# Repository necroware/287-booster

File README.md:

# 287 Booster

This is an interposer which adds a jumper which can be used to select the clock
divider on a 287 floating point unit. It was designed and open sourced in
cooperation with the user i440bx from the German dosreloaded.de community.

## Background

Intel 287 co-processors have configuration pin 39 for the clock mode signal
(CKM) setup. When this pin is pulled up the chip will use the clock directly. If
it is pulled to ground the chip will use a clock divider. The pin has internal
pull-down resistor, so it can be left unconnected, which will default the
setting to divided clock. Which divider will be used depends on the chip:

- Intel D80287, M80287 run at 1/3 of the clock
- Intel i287XL runs at 1/2 of the clock
- AMD D80C287 runs at 1/3 of the clock

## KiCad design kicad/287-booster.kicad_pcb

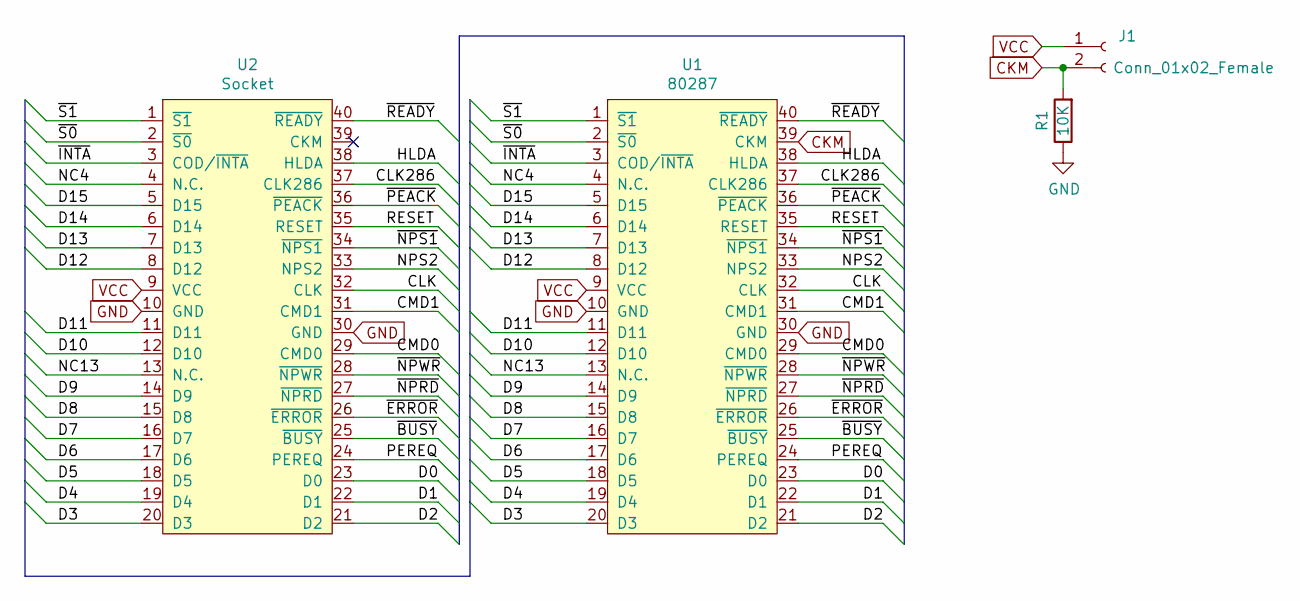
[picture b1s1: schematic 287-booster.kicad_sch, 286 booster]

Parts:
J1: Conn_01x02_Female; PinHeader_1x02_P2.54mm_Vertical
R1: 10K; R_Axial_DIN0207_L6.3mm_D2.5mm_P7.62mm_Horizontal
U1: 80287; DIP-40_W15.24mm_Socket
U2: Socket; DIP-40_W15.24mm

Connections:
/CLK: U1.32 (CLK), U2.32 (CLK)
/CLK286: U1.37 (CLK286), U2.37 (CLK286)
/CMD0: U1.29 (CMD0), U2.29 (CMD0)
/CMD1: U1.31 (CMD1), U2.31 (CMD1)
/D0: U1.23 (D0), U2.23 (D0)
/D1: U1.22 (D1), U2.22 (D1)
/D2: U1.21 (D2), U2.21 (D2)
/D3: U1.20 (D3), U2.20 (D3)
/D4: U1.19 (D4), U2.19 (D4)
/D5: U1.18 (D5), U2.18 (D5)
/D6: U1.17 (D6), U2.17 (D6)
/D7: U1.16 (D7), U2.16 (D7)
/D8: U1.15 (D8), U2.15 (D8)
/D9: U1.14 (D9), U2.14 (D9)
/D10: U1.12 (D10), U2.12 (D10)
/D11: U1.11 (D11), U2.11 (D11)
/D12: U1.8 (D12), U2.8 (D12)
/D13: U1.7 (D13), U2.7 (D13)
/D14: U1.6 (D14), U2.6 (D14)
/D15: U1.5 (D15), U2.5 (D15)
/HLDA: U1.38 (HLDA), U2.38 (HLDA)
/NC4: U1.4 (N.C.), U2.4 (N.C.)
/NC13: U1.13 (N.C.), U2.13 (N.C.)
/NPS2: U1.33 (NPS2), U2.33 (NPS2)
/PEREQ: U1.24 (PEREQ), U2.24 (PEREQ)
/RESET: U1.35 (RESET), U2.35 (RESET)
/~BUSY: U1.25 (~BUSY), U2.25 (~BUSY)
/~ERROR: U1.26 (~ERROR), U2.26 (~ERROR)
/~INTA: U1.3 (COD/~INTA), U2.3 (COD/~INTA)
/~NPRD: U1.27 (~NPRD), U2.27 (~NPRD)
/~NPS1: U1.34 (~NPS1), U2.34 (~NPS1)
/~NPWR: U1.28 (~NPWR), U2.28 (~NPWR)
/~PEACK: U1.36 (~PEACK), U2.36 (~PEACK)
/~READY: U1.40 (~READY), U2.40 (~READY)
/~S0: U1.2 (~S0), U2.2 (~S0)
/~S1: U1.1 (~S1), U2.1 (~S1)
CKM: J1.2, R1.2, U1.39 (CKM)
GND: R1.1, U1.10 (GND), U1.30 (GND), U2.10 (GND), U2.30 (GND)
VCC: J1.1, U1.9 (VCC), U2.9 (VCC)

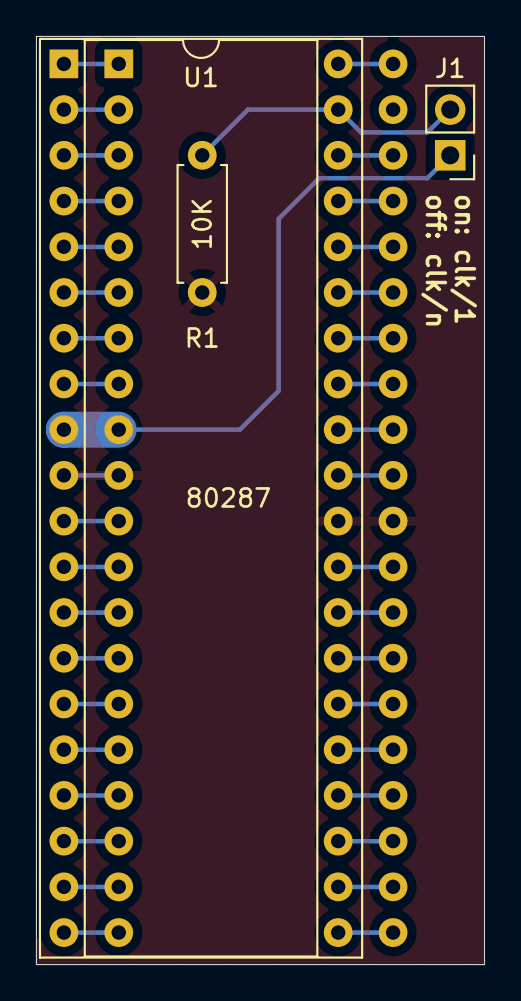
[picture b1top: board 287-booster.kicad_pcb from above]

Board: 2 copper layers, 24.9 x 51.6 mm, 4 parts (0 on the bottom side), 39 nets.

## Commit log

2023-02-27 Switched to KiCad 7
2024-05-06 Updated project to KiCad 8
2025-05-03 Update to KiCad 9
2025-05-03 add readme
2025-05-03 add license
2025-05-15 Fix readme, add picture
2025-05-15 rotated text
2025-05-15 ignore gerber folder
